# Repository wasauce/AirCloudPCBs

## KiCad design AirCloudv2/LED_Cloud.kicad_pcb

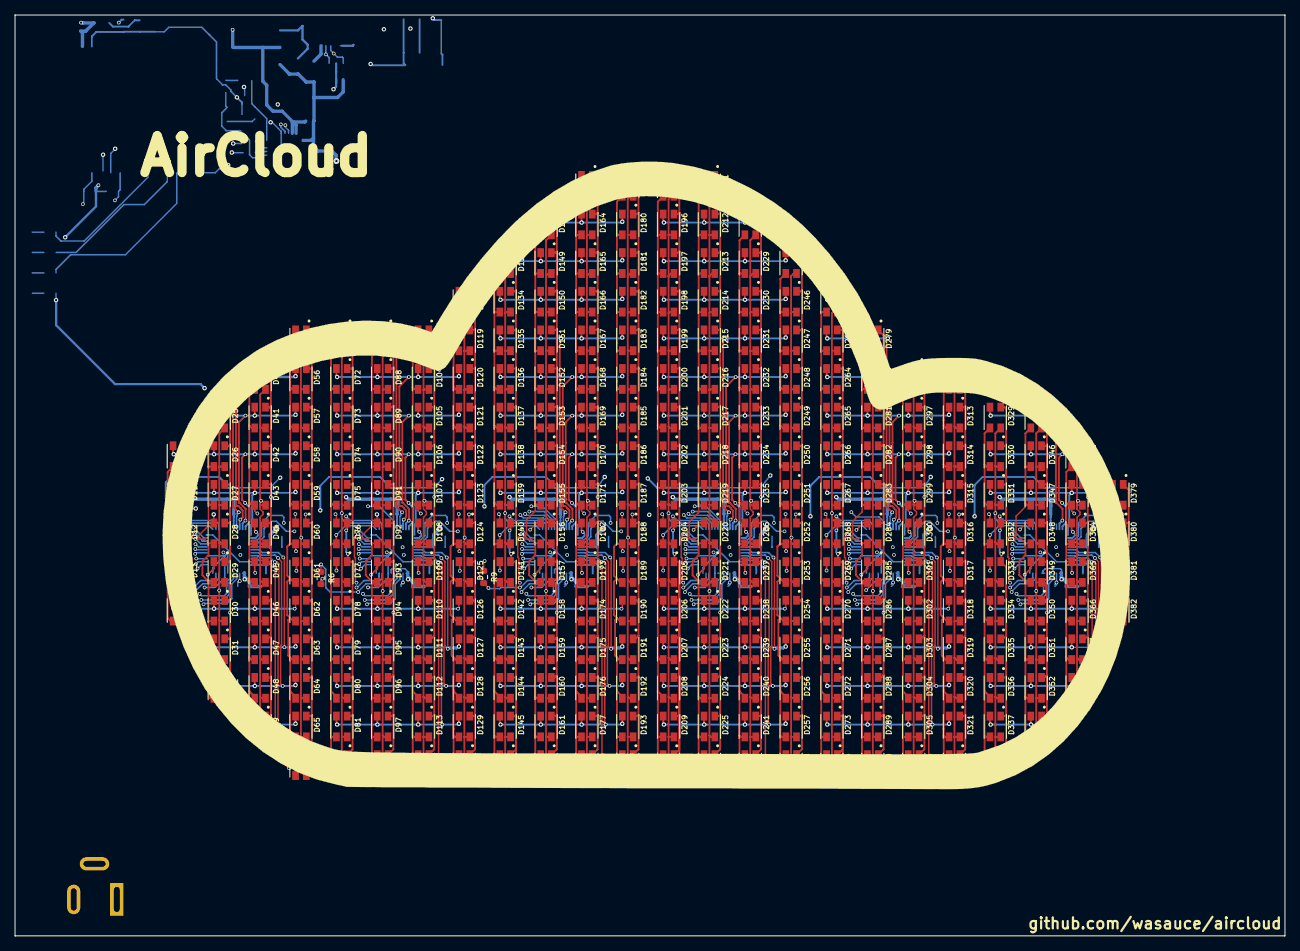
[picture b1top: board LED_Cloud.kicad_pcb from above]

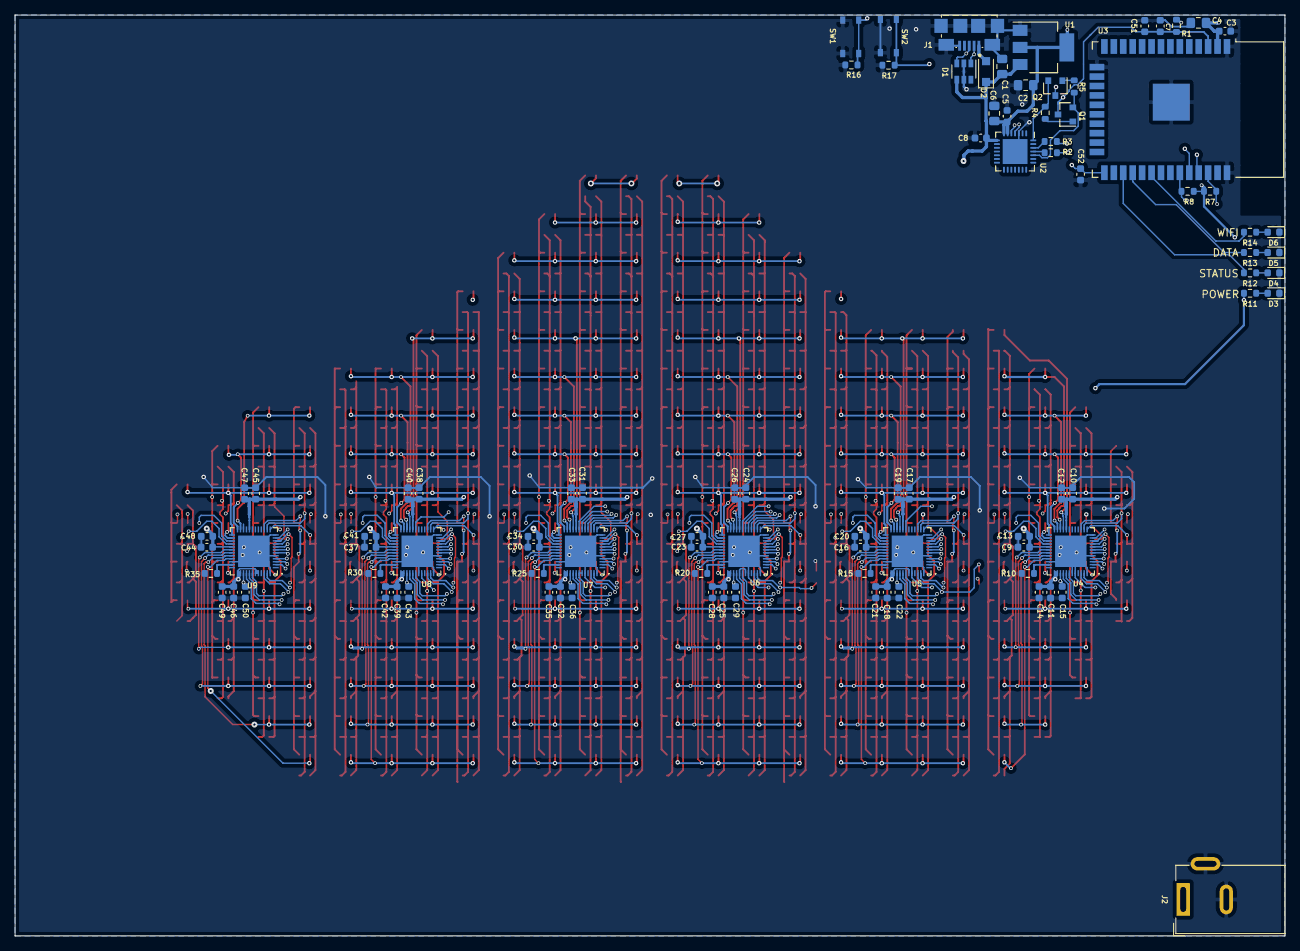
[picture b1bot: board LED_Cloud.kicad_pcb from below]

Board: 4 copper layers, 171.0 x 124.0 mm, 377 parts (92 on the bottom side), 186 nets.

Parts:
C1, C2, C4: CL21A226MOCLRNC; C_0805_2012Metric_Pad1.15x1.40mm_HandSolder
C3, C5, C7, C8, C12, C13, C14, C19, C20, C21, C26, C27, C28, C33, C34, C35, C40, C41, C42, C47, C48, C49, C51, C52: CC0603ZRY5V9BB104; C_0603_1608Metric
C6: CL21A475KQFNNNE; C_0805_2012Metric_Pad1.15x1.40mm_HandSolder
C9, C10, C11, C15, C16, C17, C18, C22, C23, C24, C25, C29, C30, C31, C32, C36, C37, C38, C39, C43, C44, C45, C46, C50: 885012106020; C_0603_1608Metric
D1: DSS15UTR; D_SOD-123F
D2: ESDA6V1BC6; SOT-23-6
D3, D4, D5, D6: 19-113Z/T1D-CP2Q2HY/3T; LED_0603_1608Metric
D10, D11, D12, D13, D14, D25, D26, D27, D28, D29, D30, D31, D32, D40, D41, D42, D43, D44, D45, D46, D47, D48, D49, D55, D56, D57, D58, D59, D60, D61, D62, D63, D64, D65, D66, D71, D72, D73, D74, D75, D76, D77, D78, D79, D80, D81, D82, D87, D88, D89, D90, D91, D92, D93, D94, D95, D96, D97, D98, D103, D104, D105, D106, D107, D108, D109, D110, D111, D112, D113, D114, D118, D119, D120, D121, D122, D123, D124, D125, D126, D127, D128, D129, D130, D133, D134, D135, D136, D137, D138, D139, D140, D141, D142, D143, D144, D145, D146, D148, D149, D150, D151, D152, D153, D154, D155, D156, D157, D158, D159, D160, D161, D162, D163, D164, D165, D166, D167, D168, D169, D170, D171, D172, D173, D174, D175, D176, D177, D178, D179, D180, D181, D182, D183, D184, D185, D186, D187, D188, D189, D190, D191, D192, D193, D194, D195, D196, D197, D198, D199, D200, D201, D202, D203, D204, D205, D206, D207, D208, D209, D210, D211, D212, D213, D214, D215, D216, D217, D218, D219, D220, D221, D222, D223, D224, D225, D226, D228, D229, D230, D231, D232, D233, D234, D235, D236, D237, D238, D239, D240, D241, D242, D245, D246, D247, D248, D249, D250, D251, D252, D253, D254, D255, D256, D257, D258, D262, D263, D264, D265, D266, D267, D268, D269, D270, D271, D272, D273, D274, D279, D280, D281, D282, D283, D284, D285, D286, D287, D288, D289, D290, D296, D297, D298, D299, D300, D301, D302, D303, D304, D305, D306, D312, D313, D314, D315, D316, D317, D318, D319, D320, D321, D322, D329, D330, D331, D332, D333, D334, D335, D336, D337, D338, D345, D346, D347, D348, D349, D350, D351, D352, D353, D362, D363, D364, D365, D366, D367, D368, D379, D380, D381, D382: XZM2CRKM2DGFBB45SCCB; LED_XZM2CRKM2DGFBB45SCCB
J1: 10118192-0001LF; AMPHENOL_10118192-0001LF
J2: 694108301002; BarrelJack_Wuerth_6941xx301002
Q1, Q2: MMSS8050-L-TP; SOT-23
R1, R4, R5, R6, R7, R8, R9, R16, R17: RC0603JR-0710KL; R_0603_1608Metric
R2, R3: RC0603FR-070RL; R_0603_1608Metric
R10, R15, R20, R25, R30, R35: RNCP0603FTD20K0; R_0603_1608Metric
R11, R12, R13, R14: CRGCQ0603J330R; R_0603_1608Metric
SW1, SW2: PTS815 SJM 250 SMTR LFS; PTS815_SJM_250_SMTR_LFS
U1: NCP1117LPST33T3G; SOT-223-3_TabPin2
U2: CP2102N-A02-GQFN28R; QFN-28-1EP_5x5mm_P0.5mm_EP3.35x3.35mm
U3: ESP32-WROOM-32D (16MB); ESP32-WROOM-32
U4, U5, U6, U7, U8, U9: IS31FL3733-QFLS4-TR

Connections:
+3V3: C2.2, C3.2, C4.2, C5.2, C6.2, C15.1, C22.1, C29.1, C36.1, C43.1, C50.1, R1.2, R6.2, R7.2, R8.2, R11.2, U1.2, U2.6, U2.7, U3.2, U4.39, U5.39, U6.39, U7.39, U8.39, U9.39
DTR: Q2.2, R4.2, U2.28
EN: C7.2, C51.1, Q1.3, R1.1, R16.2, SW1.2, U3.3
GND: C1.1, C2.1, C3.1, C4.1, C5.1, C6.1, C7.1, C8.1, C9.2, C10.2, C11.2, C12.2, C13.2, C14.2, C15.2, C16.2, C17.2, C18.2, C19.2, C20.2, C21.2, C22.2, C23.2, C24.2, C25.2, C26.2, C27.2, C28.2, C29.2, C30.2, C31.2, C32.2, C33.2, C34.2, C35.2, C36.2, C37.2, C38.2, C39.2, C40.2, C41.2, C42.2, C43.2, C44.2, C45.2, C46.2, C47.2, C48.2, C49.2, C50.2, C51.2, C52.2, D2.2, D2.5, D3.1, D4.1, D5.1, D6.1, J1.5, J1.SH1, J1.SH2, J1.SH3, J1.SH4, J1.SH5, J1.SH6, J2.2, J2.3, R9.1, R10.1, R15.1, R16.1, R17.1, R20.1, R25.1, R30.1, R35.1, SW1.1, SW2.1, U1.1, U2.3, U2.29, U3.1, U3.15, U3.38, U3.39, U4.5, U4.12, U4.34, U4.43, U4.44, U4.48, U4.49, U5.5, U5.12, U5.34, U5.44, U5.48, U5.49, U6.5, U6.12, U6.34, U6.44, U6.48, U6.49, U7.5, U7.12, U7.34, U7.44, U7.48, U7.49, U8.5, U8.12, U8.34, U8.43, U8.48, U8.49, U9.5, U9.12, U9.34, U9.48, U9.49
IICRST: R9.2, U4.47, U5.47, U6.47, U7.47, U8.47, U9.47
IO_0: C52.1, Q2.3, R17.2, SW2.2, U3.25
unnamed: D1.2, J1.1
unnamed: D3.2, R11.1
unnamed: D4.2, R12.1
unnamed: D5.2, R13.1
unnamed: D6.2, R14.1
unnamed: D10.1, D11.1, D12.1, D13.1, D14.1, U4.15
unnamed: D10.2, D11.2, D12.2, D13.2, D14.2, U4.14
unnamed: D10.3, D11.3, D12.3, D13.3, D14.3, U4.13
unnamed: D10.4, D26.4, D42.4, D58.4, U4.24
unnamed: D11.4, D27.4, D43.4, D59.4, U4.25
unnamed: D12.4, D28.4, D44.4, D60.4, U4.26
unnamed: D13.4, D29.4, D45.4, D61.4, U4.27
unnamed: D14.4, D30.4, D46.4, D62.4, U4.28
unnamed: D25.1, D26.1, D27.1, D28.1, D29.1, D30.1, D31.1, D32.1, U4.11
unnamed: D25.2, D26.2, D27.2, D28.2, D29.2, D30.2, D31.2, D32.2, U4.10
unnamed: D25.3, D26.3, D27.3, D28.3, D29.3, D30.3, D31.3, D32.3, U4.9
unnamed: D25.4, D41.4, D57.4, U4.23
unnamed: D31.4, D47.4, D63.4, U4.30
unnamed: D32.4, D48.4, D64.4, U4.31
unnamed: D40.1, D41.1, D42.1, D43.1, D44.1, D45.1, D46.1, D47.1, D48.1, D49.1, U4.8
unnamed: D40.2, D41.2, D42.2, D43.2, D44.2, D45.2, D46.2, D47.2, D48.2, D49.2, U4.7
unnamed: D40.3, D41.3, D42.3, D43.3, D44.3, D45.3, D46.3, D47.3, D48.3, D49.3, U4.6
unnamed: D40.4, D56.4, U4.22
unnamed: D49.4, D65.4, U4.32
unnamed: D55.1, D56.1, D57.1, D58.1, D59.1, D60.1, D61.1, D62.1, D63.1, D64.1, D65.1, D66.1, U4.4
unnamed: D55.2, D56.2, D57.2, D58.2, D59.2, D60.2, D61.2, D62.2, D63.2, D64.2, D65.2, D66.2, U4.3
unnamed: D55.3, D56.3, D57.3, D58.3, D59.3, D60.3, D61.3, D62.3, D63.3, D64.3, D65.3, D66.3, U4.2
unnamed: D55.4, U4.21
unnamed: D66.4, U4.33
unnamed: D71.1, D72.1, D73.1, D74.1, D75.1, D76.1, D77.1, D78.1, D79.1, D80.1, D81.1, D82.1, U5.15
unnamed: D71.2, D72.2, D73.2, D74.2, D75.2, D76.2, D77.2, D78.2, D79.2, D80.2, D81.2, D82.2, U5.14
unnamed: D71.3, D72.3, D73.3, D74.3, D75.3, D76.3, D77.3, D78.3, D79.3, D80.3, D81.3, D82.3, U5.13
unnamed: D87.1, D88.1, D89.1, D90.1, D91.1, D92.1, D93.1, D94.1, D95.1, D96.1, D97.1, D98.1, U5.11
unnamed: D87.2, D88.2, D89.2, D90.2, D91.2, D92.2, D93.2, D94.2, D95.2, D96.2, D97.2, D98.2, U5.10
unnamed: D87.3, D88.3, D89.3, D90.3, D91.3, D92.3, D93.3, D94.3, D95.3, D96.3, D97.3, D98.3, U5.9
unnamed: D103.1, D104.1, D105.1, D106.1, D107.1, D108.1, D109.1, D110.1, D111.1, D112.1, D113.1, D114.1, U5.8
unnamed: D103.2, D104.2, D105.2, D106.2, D107.2, D108.2, D109.2, D110.2, D111.2, D112.2, D113.2, D114.2, U5.7
unnamed: D103.3, D104.3, D105.3, D106.3, D107.3, D108.3, D109.3, D110.3, D111.3, D112.3, D113.3, D114.3, U5.6
unnamed: D71.4, D87.4, D103.4, D119.4, U5.21
unnamed: D72.4, D88.4, D104.4, D120.4, U5.22
unnamed: D73.4, D89.4, D105.4, D121.4, U5.23
unnamed: D74.4, D90.4, D106.4, D122.4, U5.24
unnamed: D75.4, D91.4, D107.4, D123.4, U5.25
unnamed: D76.4, D92.4, D108.4, D124.4, U5.26
unnamed: D77.4, D93.4, D109.4, D125.4, U5.27
unnamed: D78.4, D94.4, D110.4, D126.4, U5.28
unnamed: D79.4, D95.4, D111.4, D127.4, U5.30
unnamed: D80.4, D96.4, D112.4, D128.4, U5.31
unnamed: D81.4, D97.4, D113.4, D129.4, U5.32
unnamed: D82.4, D98.4, D114.4, D130.4, U5.33
unnamed: D118.1, D119.1, D120.1, D121.1, D122.1, D123.1, D124.1, D125.1, D126.1, D127.1, D128.1, D129.1, D130.1, U5.4
unnamed: D118.2, D119.2, D120.2, D121.2, D122.2, D123.2, D124.2, D125.2, D126.2, D127.2, D128.2, D129.2, D130.2, U5.3
unnamed: D118.3, D119.3, D120.3, D121.3, D122.3, D123.3, D124.3, D125.3, D126.3, D127.3, D128.3, D129.3, D130.3, U5.2
unnamed: D118.4, U5.19
unnamed: D133.1, D134.1, D135.1, D136.1, D137.1, D138.1, D139.1, D140.1, D141.1, D142.1, D143.1, D144.1, D145.1, D146.1, U6.15
unnamed: D133.2, D134.2, D135.2, D136.2, D137.2, D138.2, D139.2, D140.2, D141.2, D142.2, D143.2, D144.2, D145.2, D146.2, U6.14
unnamed: D133.3, D134.3, D135.3, D136.3, D137.3, D138.3, D139.3, D140.3, D141.3, D142.3, D143.3, D144.3, D145.3, D146.3, U6.13
unnamed: D133.4, D149.4, D165.4, D181.4, U6.18
unnamed: D134.4, D150.4, D166.4, D182.4, U6.19
unnamed: D135.4, D151.4, D167.4, D183.4, U6.21
unnamed: D136.4, D152.4, D168.4, D184.4, U6.22
unnamed: D137.4, D153.4, D169.4, D185.4, U6.23
unnamed: D138.4, D154.4, D170.4, D186.4, U6.24
unnamed: D139.4, D155.4, D171.4, D187.4, U6.25
unnamed: D140.4, D156.4, D172.4, D188.4, U6.26
unnamed: D141.4, D157.4, D173.4, D189.4, U6.27
unnamed: D142.4, D158.4, D174.4, D190.4, U6.28
unnamed: D143.4, D159.4, D175.4, D191.4, U6.30
unnamed: D144.4, D160.4, D176.4, D192.4, U6.31
unnamed: D145.4, D161.4, D177.4, D193.4, U6.32
unnamed: D146.4, D162.4, D178.4, D194.4, U6.33
unnamed: D148.1, D149.1, D150.1, D151.1, D152.1, D153.1, D154.1, D155.1, D156.1, D157.1, D158.1, D159.1, D160.1, D161.1, D162.1, U6.11
unnamed: D148.2, D149.2, D150.2, D151.2, D152.2, D153.2, D154.2, D155.2, D156.2, D157.2, D158.2, D159.2, D160.2, D161.2, D162.2, U6.10
unnamed: D148.3, D149.3, D150.3, D151.3, D152.3, D153.3, D154.3, D155.3, D156.3, D157.3, D158.3, D159.3, D160.3, D161.3, D162.3, U6.9
unnamed: D148.4, D164.4, D180.4, U6.17
unnamed: D163.1, D164.1, D165.1, D166.1, D167.1, D168.1, D169.1, D170.1, D171.1, D172.1, D173.1, D174.1, D175.1, D176.1, D177.1, D178.1, U6.8
unnamed: D163.2, D164.2, D165.2, D166.2, D167.2, D168.2, D169.2, D170.2, D171.2, D172.2, D173.2, D174.2, D175.2, D176.2, D177.2, D178.2, U6.7
unnamed: D163.3, D164.3, D165.3, D166.3, D167.3, D168.3, D169.3, D170.3, D171.3, D172.3, D173.3, D174.3, D175.3, D176.3, D177.3, D178.3, U6.6
unnamed: D163.4, D179.4, U6.16
unnamed: D179.1, D180.1, D181.1, D182.1, D183.1, D184.1, D185.1, D186.1, D187.1, D188.1, D189.1, D190.1, D191.1, D192.1, D193.1, D194.1, U6.4
unnamed: D179.2, D180.2, D181.2, D182.2, D183.2, D184.2, D185.2, D186.2, D187.2, D188.2, D189.2, D190.2, D191.2, D192.2, D193.2, D194.2, U6.3
unnamed: D179.3, D180.3, D181.3, D182.3, D183.3, D184.3, D185.3, D186.3, D187.3, D188.3, D189.3, D190.3, D191.3, D192.3, D193.3, D194.3, U6.2
unnamed: D195.1, D196.1, D197.1, D198.1, D199.1, D200.1, D201.1, D202.1, D203.1, D204.1, D205.1, D206.1, D207.1, D208.1, D209.1, D210.1, U7.15
unnamed: D195.2, D196.2, D197.2, D198.2, D199.2, D200.2, D201.2, D202.2, D203.2, D204.2, D205.2, D206.2, D207.2, D208.2, D209.2, D210.2, U7.14
unnamed: D195.3, D196.3, D197.3, D198.3, D199.3, D200.3, D201.3, D202.3, D203.3, D204.3, D205.3, D206.3, D207.3, D208.3, D209.3, D210.3, U7.13
unnamed: D195.4, D211.4, U7.16
unnamed: D196.4, D212.4, D228.4, U7.17
unnamed: D197.4, D213.4, D229.4, D245.4, U7.18
unnamed: D198.4, D214.4, D230.4, D246.4, U7.19
unnamed: D199.4, D215.4, D231.4, D247.4, U7.21
unnamed: D200.4, D216.4, D232.4, D248.4, U7.22
unnamed: D201.4, D217.4, D233.4, D249.4, U7.23
unnamed: D202.4, D218.4, D234.4, D250.4, U7.24
unnamed: D203.4, D219.4, D235.4, D251.4, U7.25
unnamed: D204.4, D220.4, D236.4, D252.4, U7.26
unnamed: D205.4, D221.4, D237.4, D253.4, U7.27
unnamed: D206.4, D222.4, D238.4, D254.4, U7.28
unnamed: D207.4, D223.4, D239.4, D255.4, U7.30
unnamed: D208.4, D224.4, D240.4, D256.4, U7.31
unnamed: D209.4, D225.4, D241.4, D257.4, U7.32
unnamed: D210.4, D226.4, D242.4, D258.4, U7.33
unnamed: D211.1, D212.1, D213.1, D214.1, D215.1, D216.1, D217.1, D218.1, D219.1, D220.1, D221.1, D222.1, D223.1, D224.1, D225.1, D226.1, U7.11
unnamed: D211.2, D212.2, D213.2, D214.2, D215.2, D216.2, D217.2, D218.2, D219.2, D220.2, D221.2, D222.2, D223.2, D224.2, D225.2, D226.2, U7.10
unnamed: D211.3, D212.3, D213.3, D214.3, D215.3, D216.3, D217.3, D218.3, D219.3, D220.3, D221.3, D222.3, D223.3, D224.3, D225.3, D226.3, U7.9
unnamed: D228.1, D229.1, D230.1, D231.1, D232.1, D233.1, D234.1, D235.1, D236.1, D237.1, D238.1, D239.1, D240.1, D241.1, D242.1, U7.8
unnamed: D228.2, D229.2, D230.2, D231.2, D232.2, D233.2, D234.2, D235.2, D236.2, D237.2, D238.2, D239.2, D240.2, D241.2, D242.2, U7.7
unnamed: D228.3, D229.3, D230.3, D231.3, D232.3, D233.3, D234.3, D235.3, D236.3, D237.3, D238.3, D239.3, D240.3, D241.3, D242.3, U7.6
unnamed: D245.1, D246.1, D247.1, D248.1, D249.1, D250.1, D251.1, D252.1, D253.1, D254.1, D255.1, D256.1, D257.1, D258.1, U7.4
unnamed: D245.2, D246.2, D247.2, D248.2, D249.2, D250.2, D251.2, D252.2, D253.2, D254.2, D255.2, D256.2, D257.2, D258.2, U7.3
unnamed: D245.3, D246.3, D247.3, D248.3, D249.3, D250.3, D251.3, D252.3, D253.3, D254.3, D255.3, D256.3, D257.3, D258.3, U7.2
unnamed: D262.1, D263.1, D264.1, D265.1, D266.1, D267.1, D268.1, D269.1, D270.1, D271.1, D272.1, D273.1, D274.1, U8.15
unnamed: D262.2, D263.2, D264.2, D265.2, D266.2, D267.2, D268.2, D269.2, D270.2, D271.2, D272.2, D273.2, D274.2, U8.14
unnamed: D262.3, D263.3, D264.3, D265.3, D266.3, D267.3, D268.3, D269.3, D270.3, D271.3, D272.3, D273.3, D274.3, U8.13
unnamed: D262.4, U8.19
unnamed: D263.4, D279.4, U8.21
unnamed: D264.4, D280.4, D296.4, D312.4, U8.22
unnamed: D265.4, D281.4, D297.4, D313.4, U8.23
unnamed: D266.4, D282.4, D298.4, D314.4, U8.24
unnamed: D267.4, D283.4, D299.4, D315.4, U8.25
unnamed: D268.4, D284.4, D300.4, D316.4, U8.26
unnamed: D269.4, D285.4, D301.4, D317.4, U8.27
unnamed: D270.4, D286.4, D302.4, D318.4, U8.28
unnamed: D271.4, D287.4, D303.4, D319.4, U8.30
unnamed: D272.4, D288.4, D304.4, D320.4, U8.31
unnamed: D273.4, D289.4, D305.4, D321.4, U8.32
unnamed: D274.4, D290.4, D306.4, D322.4, U8.33
unnamed: D279.1, D280.1, D281.1, D282.1, D283.1, D284.1, D285.1, D286.1, D287.1, D288.1, D289.1, D290.1, U8.11
unnamed: D279.2, D280.2, D281.2, D282.2, D283.2, D284.2, D285.2, D286.2, D287.2, D288.2, D289.2, D290.2, U8.10
unnamed: D279.3, D280.3, D281.3, D282.3, D283.3, D284.3, D285.3, D286.3, D287.3, D288.3, D289.3, D290.3, U8.9
unnamed: D296.1, D297.1, D298.1, D299.1, D300.1, D301.1, D302.1, D303.1, D304.1, D305.1, D306.1, U8.8
unnamed: D296.2, D297.2, D298.2, D299.2, D300.2, D301.2, D302.2, D303.2, D304.2, D305.2, D306.2, U8.7
unnamed: D296.3, D297.3, D298.3, D299.3, D300.3, D301.3, D302.3, D303.3, D304.3, D305.3, D306.3, U8.6
unnamed: D312.1, D313.1, D314.1, D315.1, D316.1, D317.1, D318.1, D319.1, D320.1, D321.1, D322.1, U8.4
unnamed: D312.2, D313.2, D314.2, D315.2, D316.2, D317.2, D318.2, D319.2, D320.2, D321.2, D322.2, U8.3
unnamed: D312.3, D313.3, D314.3, D315.3, D316.3, D317.3, D318.3, D319.3, D320.3, D321.3, D322.3, U8.2
unnamed: D329.1, D330.1, D331.1, D332.1, D333.1, D334.1, D335.1, D336.1, D337.1, D338.1, U9.15
unnamed: D329.2, D330.2, D331.2, D332.2, D333.2, D334.2, D335.2, D336.2, D337.2, D338.2, U9.14
unnamed: D329.3, D330.3, D331.3, D332.3, D333.3, D334.3, D335.3, D336.3, D337.3, D338.3, U9.13
unnamed: D329.4, D345.4, U9.23
unnamed: D330.4, D346.4, D362.4, U9.24
unnamed: D331.4, D347.4, D363.4, D379.4, U9.25
unnamed: D332.4, D348.4, D364.4, D380.4, U9.26
unnamed: D333.4, D349.4, D365.4, D381.4, U9.27
unnamed: D334.4, D350.4, D366.4, D382.4, U9.28
unnamed: D335.4, D351.4, D367.4, U9.30
unnamed: D336.4, D352.4, D368.4, U9.31
unnamed: D337.4, D353.4, U9.32
unnamed: D338.4, U9.33
unnamed: D345.1, D346.1, D347.1, D348.1, D349.1, D350.1, D351.1, D352.1, D353.1, U9.11
unnamed: D345.2, D346.2, D347.2, D348.2, D349.2, D350.2, D351.2, D352.2, D353.2, U9.10
unnamed: D345.3, D346.3, D347.3, D348.3, D349.3, D350.3, D351.3, D352.3, D353.3, U9.9
unnamed: D362.1, D363.1, D364.1, D365.1, D366.1, D367.1, D368.1, U9.8
unnamed: D362.2, D363.2, D364.2, D365.2, D366.2, D367.2, D368.2, U9.7
unnamed: D362.3, D363.3, D364.3, D365.3, D366.3, D367.3, D368.3, U9.6
unnamed: D379.1, D380.1, D381.1, D382.1, U9.4
unnamed: D379.2, D380.2, D381.2, D382.2, U9.3
unnamed: D379.3, D380.3, D381.3, D382.3, U9.2
unnamed: Q1.1, R4.1
unnamed: Q2.1, R5.1
unnamed: R2.2, U2.25
unnamed: R3.2, U2.26
unnamed: R10.2, U4.35
unnamed: R12.2, U3.27
unnamed: R13.2, U3.28
unnamed: R14.2, U3.30
unnamed: R15.2, U5.35
unnamed: R20.2, U6.35
unnamed: R25.2, U7.35
unnamed: R30.2, U8.35
unnamed: R35.2, U9.35
RTS: Q1.2, R5.2, U2.24
RXD_0: R3.1, U3.34
SCL: R7.1, U3.36, U4.42, U5.42, U6.42, U7.42, U7.43, U8.42, U9.42
SDA: R8.1, U3.33, U4.41, U5.41, U6.41, U6.43, U7.41, U8.41, U9.41
SDB: R6.1, U4.46, U5.46, U6.46, U7.46, U8.46, U9.46
SYNC: U4.40, U5.40, U6.40, U7.40, U8.40, U9.40
TXD_0: R2.1, U3.35
USB_D+: D2.3, J1.3, U2.4
USB_D-: D2.1, J1.2, U2.5
VBUS: C1.2, C8.2, C9.1, C10.1, C11.1, C12.1, C13.1, C14.1, C16.1, C17.1, C18.1, C19.1, C20.1, C21.1, C23.1, C24.1, C25.1, C26.1, C27.1, C28.1, C30.1, C31.1, C32.1, C33.1, C34.1, C35.1, C37.1, C38.1, C39.1, C40.1, C41.1, C42.1, C44.1, C45.1, C46.1, C47.1, C48.1, C49.1, D1.1, D2.4, J2.1, U1.3, U2.8, U4.20, U4.29, U4.37, U4.38, U5.20, U5.29, U5.37, U5.38, U5.43, U6.20, U6.29, U6.37, U6.38, U7.20, U7.29, U7.37, U7.38, U8.20, U8.29, U8.37, U8.38, U8.44, U9.20, U9.29, U9.37, U9.38, U9.43, U9.44

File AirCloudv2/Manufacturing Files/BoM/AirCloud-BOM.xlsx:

References | Description | Digikey Part # | Manufacturer | Manufacturer Part Number | Quantity
C3, C5, C7, C8, C12, C13, C14, C19, C20, C21, C26, C27, C28,C33, C34, C35, C40,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 | -20%, +80% 50V Ceramic Capacitor Y5V (F) 0603 (1608 Metric) | 311-1343-1-ND | Yageo | CC0603ZRY5V9BB104 | 24
C9, C10, C11, C15, C16, C17, C18, C22, C23, C24, C25, C29,C30, C31, C32, C36, C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 | 0.47µF ±20% 25V Ceramic Capacitor X5R 0603 (1608 Metric) | 732-7917-1-ND | Würth Elektronik | 885012106020 | 24
C1, C2, C4 | 22µF ±20% 16V Ceramic Capacitor X5R 0805 (2012 Metric) | 1276-6780-1-ND | Samsung Electro-Mechanics | CL21A226MOCLRNC | 3
C6 | 4.7µF ±10% 6.3V Ceramic Capacitor X5R 0805 (2012 Metric) | 1276-1198-1-ND | Samsung Electro-Mechanics | CL21A475KQFNNNE | 1
D2 | Clamp Ipp Tvs Diode Surface Mount SOT-23-6 | 497-6635-1-ND | STMicroelectronics | ESDA6V1BC6 | 1
D1 | Diode Schottky 1A Surface Mount SOD-123FL | 1655-1928-1-ND | SMC Diode Solutions | DSS15UTR | 1
D3, D4, D5, D6 | White LED Indication - Discrete 2.925V 0603 (1608 Metric) | 1080-1573-1-ND | Everlight Electronics Co Ltd | 19-113Z/T1D-CP2Q2HY/3T | 4
D10, D11, D12, D13, D14, D25, D26, D27, D28, D29, D30, D31, D32, D40, D41, D42,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 | Red, Green, Blue (RGB) 625nm Red, 525nm Green, 470nm Blue LED Indication - Disc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 |  | SunLED | XZM2CRKM2DGFBB45SCCB | 285
J1 | USB - micro B USB 2.0 Receptacle Connector 5 Position Surface Mount, Right Angle | 609-4613-1-ND | Amphenol ICC (FCI) | 10118192-0001LF | 1
J2 | Power Barrel Connector Jack 2.50mm ID (0.098"), 5.50mm OD (0.217") Through Hole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 | 732-5934-ND | Würth Elektronik | 694108301002 | 1
R25, R30, R35 | 20 kOhms ±1% 0.125W, 1/8W Chip Resistor 0603 (1608 Metric) Anti-Sulfur, Moistur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 | RNCP0603FTD20K0CT-ND | Stackpole Electronics Inc | RNCP0603FTD20K0 | 3
R2, R3 | 0 Ohms Jumper 0.1W, 1/10W Chip Resistor 0603 (1608 Metric) Thick Film | 311-0.0HRCT-ND | Yageo | RC0603FR-070RL | 2
R1, R4, R5, R6, R7, R8, R9, R16, R17 | 10 kOhms ±5% 0.1W, 1/10W Chip Resistor 0603 (1608 Metric) Thick Film | 311-10KGRCT-ND | Yageo | RC0603JR-0710KL | 9
R11, R12, R13, R14 | 10 kOhms ±5% 0.1W, 1/10W Chip Resistor 0603 (1608 Metric) Thick Film | 311-10KGRCT-ND | Yageo | RC0603JR-0710KL | 4
R10, R15, R20 | 20 kOhms ±1% 0.125W, 1/8W Chip Resistor 0603 (1608 Metric) Anti-Sulfur, Moistur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 | RNCP0603FTD20K0CT-ND | Stackpole Electronics Inc | RNCP0603FTD20K0 | 3
SW1, SW2 | Tactile Switch SPST-NO Top Actuated Surface Mount | CKN12215-1-ND | C&K | PTS815 SJM 250 SMTR LFS | 2
U3 | Bluetooth, WiFi 802.11b/g/n, Bluetooth v4.2 +EDR, Class 1, 2 and 3 Transceiver 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 | 1904-1025-1-ND | Espressif Systems | ESP32-WROOM-32D (16MB) | 1
U4, U5, U6,U7, U8, U9 | IC LED DRVR LINEAR 46MA 48QFN | 706-1509-1-ND | Lumissil Microsystems | IS31FL3733-QFLS4-TR | 6
U1 | Linear Voltage Regulator IC Output 1A SOT-223 | NCP1117LPST33T3GOSCT-ND | ON Semiconductor | NCP1117LPST33T3G | 1
U2 | USB Bridge, USB to UART USB 2.0 UART Interface 28-QFN (5x5) | 336-5890-1-ND | Silicon Labs | CP2102N-A02-GQFN28R | 1
Q1, Q2 | Bipolar (BJT) Transistor NPN 100MHz Surface Mount SOT-23 | MMSS8050-L-TPMSCT-ND | Micro Commercial Co | MMSS8050-L-TP | 2

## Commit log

2021-05-02 aircloud v1 and v2
2021-08-23 AirCloud v3 design

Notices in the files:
parts and their libraries:
Copyright 2016 Accelerated Designs. All rights reserved.
